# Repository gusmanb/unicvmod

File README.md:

# UniCVMod by El Dr. Gusman

This is a small circuit to convert RF output to composite video. It's a complete drop-in replacement for the astec RF modulators, just remove the old "can" and drop the circuit in it's place, as simple as that.

## Update 1.1

Added capacitor on the output to improve video quality.

## Assembly notes

JP3 and JP4 are intended to be pins on the under side of the circuit which will connect to ground and leave a bit of space between the device's board and the mod solders, they fit on the same place as the RF can has it's grounding legs. JP1 and JP2 are intended to be wired and use the inputs to the RF can.

As a final measure I use some small rubber feets under the front and back of the circuit to make it totally stable and avoid any chance of short circuit.

## Calibration notes

R1 and R2 are 500Ohm potentiometers in order to allow you to adjust the signal level according to your needs, R1 will adjust the input level and R2 will adjust the output level. Composite video should have an amplitude of 0.7v but with modern TV's and converters sometimes more signal increase the picture quality, so adjust it at your will.

## Part list

- R1, R2    -     500 Ohm trimmer
- R3        -     75 Ohm, 1/4w
- R4        -     270 Ohm, 1/4w
- C1        -     10uF 16v
- T1        -     BC337
- JP3, JP4  -     Single pin
- J1        -     RCA female (RCA-103)

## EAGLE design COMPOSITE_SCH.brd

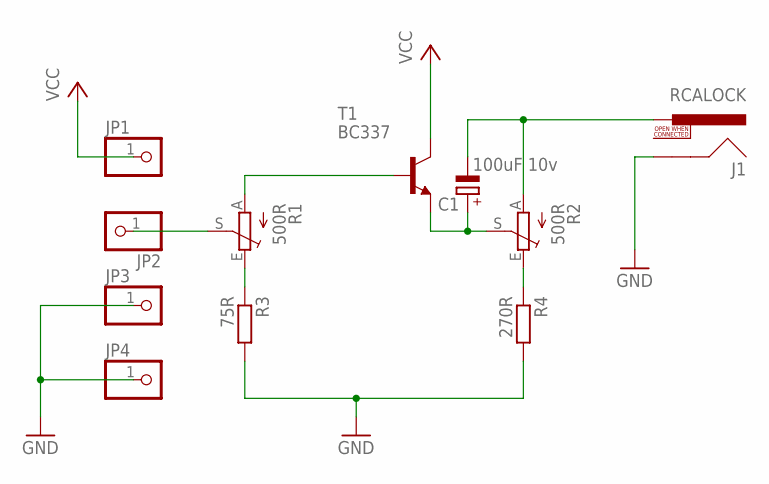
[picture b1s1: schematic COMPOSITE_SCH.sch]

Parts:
C1: 100uF 10v; E2,5-6E
J1: RCALOCK; RCA_LOCK
JP1, JP2, JP3, JP4: PINHD-1X1; 1X01
R1, R2: 500R; CA6V
R3: 75R; 0207/10
R4: 270R; 0207/10
T1: BC337; TO92

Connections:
GND: J1.SHELL, JP3.1, JP4.1, R3.2, R4.2
unnamed: R1.A, T1.2 (B)
unnamed: R1.E, R3.1
unnamed: C1.+, R2.S, T1.1 (E)
unnamed: R2.E, R4.1
unnamed: C1.-, J1.PIN, R2.A
unnamed: JP2.1, R1.S
VCC: JP1.1, T1.3 (C)

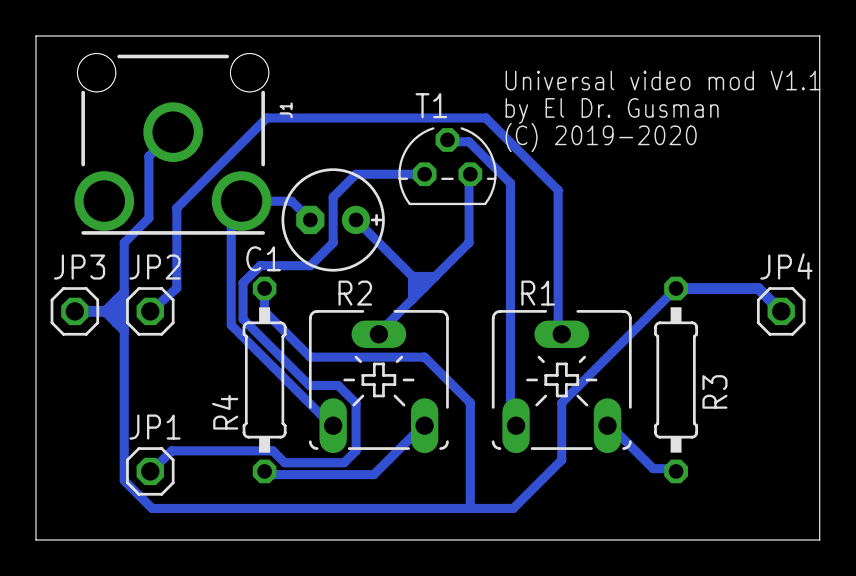
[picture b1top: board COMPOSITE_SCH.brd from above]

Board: 2 copper layers, 43.5 x 28.0 mm, 11 parts (0 on the bottom side), 8 nets.

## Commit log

2019-08-08 Added pictures of the schematic and PC, added zip file with gerber outputs ready for production
2020-01-18 Updated design to improve video quality

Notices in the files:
COMPOSITE_SCH.brd:
(C) 2019-2020
parts and their libraries:
SparkFun-Connectors: Licensing: Creative Commons ShareAlike 4.0 International - https://creativecommons.org/licenses/by-sa/4.0
